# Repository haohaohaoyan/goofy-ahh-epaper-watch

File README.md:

# Neutron e-paper watch - (relatively) low-cost interactive e-paper wristwatch for the nerdy

A developer/tech nerd friendly wristwatch powered by an ESP32 S3 MINI 1, uses an e-paper display for power efficiency, and a 2000mAh battery for all-day use. It's supposed to provide both the features that a regular watch is supposed to have, while also having smartwatch functions and IO pins to leverage the power of the ESP32 microcontroller. I really wanted to make myself a wristwatch that I could use and carry around in everyday life. I was initially inspired by that really expensive and prebuilt CircuitMess watch, but it lacked the DIY process and developer tools that I wanted (so no PineTime from Flavortown either). I also was bored and wanted to make another hardware project after Hackpad, and I started noticing how much I needed a watch because I got used to borrowing my mom's and forgetting the time afterward. Plus, it just looks cool. The e-paper screen was added for the power advantage over OLED, not drawing power asides from time changes. It made the driver bit more complex (because I didn't want to occupy more space with a drop-in driver module), but might have some orientation issues. The battery was initially going to be 500mAh, but that was much too little and I chose a much larger battery to carry a charge that should last all day at the cost of more space. I think that this will be a rewarding project and a well-functioning timepiece, but that will be settled after I order. 

Current features: 
- 1.54 inch e-paper display
- 1200 mAh Li-po battery which should have about a full day's worth of life, orange LED charging indicator
- Automatic device sleeping when not used (this takes advantage of the e-paper display to keep displaying time)
- USB-C charging and data transfer
- ESP32 S3 MINI 1 powered, for internet and Bluetooth
- Automatically syncs time with NTP every 6 hours (planned in firmware)
- 8-pin female IO pin row, with 1 ground, 1 3.3v, and 6 IO pins.
- 2 IO buttons, labeled A and B in the style of the Game Boy
- Reset and boot buttons for programming
- Hopefully won't explode (IMPORTANT)
- Hopefully won't revolt and kill me (ALSO IMPORTANT)

Firmware is currently untested (asides from the timekeeping loop) and is only there for submission purposes. It is currently in CircuitPython but I will probably rewrite it in C at one point.

Assembly notes (so far): Snip off legs on JST-PH receptacle after soldering, apply Kapton tape to the side of the battery that will lie in contact with the board, apply Kapton tape to backside of e-paper screen, use DOUBLE SIDED FOAM TAPE??? PCB should snap into case

## Schematic

## PCB
Note: the PCB is 66x36mm

3D render:

## Case

## BOM in BOM.csv, but here anyway (used a md generator, sorry)

|FIELD1                                                         |FIELD2        |FIELD3          |FIELD4                                                                                              |FIELD5     |FIELD6       |FIELD7                  |FIELD8                                                                                                                                                                                             |
|---------------------------------------------------------------|--------------|----------------|----------------------------------------------------------------------------------------------------|-----------|-------------|------------------------|---------------------------------------------------------------------------------------------------------------------------------------------------------------------------------------------------|
|Item / component                                               |Quantity      |Parts on PCB    |Link                                                                                                |Source     |Cost per unit|Total cost (no shipping)|Notes                                                                                                                                                                                              |
|PCB                                                            |5 (JLCPCB MOQ)|N/A             |JLCPCB                                                                                              |JLCPCB     |$3.74        |$18.70                  |Global Standard Direct Line, ENIG plated for reflowing. Shipping is $10.67                                                                                                                         |
|PCB Stencil                                                    |1             |N/A             |JLCPCB                                                                                              |JLCPCB     |$3.07        |$3.07                   |80x40mm to reduce weight, shipped with PCB                                                                                                                                                         |
|Case                                                           |1             |N/A             |See repository                                                                                      |           |             |                        |STEP & FreeCAD files on repository                                                                                                                                                                 |
|1200 mAh 603450 Lithium-ion polymer battery                    |1             |N/A             |https://www.amazon.com/1200mAh-Battery-Rechargeable-Lithium-Connector/dp/B09FLG39NX                 |Amazon     |$8.99        |$8.99                   |Battery JST-PH 2-pin connector may have reversed polarity, ground should be on left when slot side is facing up. Be careful or risk blowing up your room!                                          |
|1.54 inch 200x200 pixel bare e-paper display                   |1             |N/A             |https://www.waveshare.com/product/1.54inch-e-paper.htm                                              |Waveshare  |$5.99        |$5.99                   |Ribbon cable pins should be facing upwards. Don't order one of the breakout board ones!                                                                                                            |
|16mm one-piece watch strap                                     |1             |N/A             |https://www.amazon.com/WOCCI-Military-One-piece-Ballistic-Buckle/dp/B0CTSCVBB4?th=1                 |Amazon     |$6.99        |$6.99                   |Optional. Really, any strip of fabric that fits should be OK.                                                                                                                                      |
|ESP32-S3-MINI-1-N8 microcontroller                             |1             |U1              |https://www.lcsc.com/product-detail/C2913206.html                                                   |LCSC       |$4.73        |$4.73                   |                                                                                                                                                                                                   |
|G-Switch GT-USB-7010ASV USB-C receptacle                       |5 (LCSC MOQ)  |J4 or USB-C     |https://www.lcsc.com/product-detail/C2988369.html                                                   |LCSC       |$0.13        |$0.65                   |LCSC MOQ is 5, you can find another one but fitting the same footprint isn't guaranteed. I don't think it's too big of a deal considering how cheap it is and how I'll probably have to reuse them.|
|JUSHUO AFC07-S24FCA-00 24-pin .5mm pitch ribbon cable connector|5 (LCSC MOQ)  |J5              |https://www.lcsc.com/product-detail/C262567.html                                                    |LCSC       |$0.13        |$0.65                   |LCSC MOQ is 5. Make sure the contacts are on the bottom!                                                                                                                                           |
|MCP73831T-2ACI/OT battery charigng IC                          |1             |U2              |https://www.digikey.com/en/products/detail/microchip-technology/MCP73831T-2ACI-OT/964301            |Digikey    |$0.76        |$0.76                   |                                                                                                                                                                                                   |
|RT9080-33GJ5 3.3V LDO IC                                       |1             |U3              |https://www.digikey.com/en/products/detail/richtek-usa-inc/RT9080-33GJ5/6161634                     |Digikey    |$0.28        |$0.28                   |                                                                                                                                                                                                   |
|RV-3028-C7 real-time clock IC                                  |1             |U4              |https://www.digikey.com/en/products/detail/micro-crystal-ag/RV-3028-C7-32-768KHZ-1PPM-TA-QA/10499248|Digikey    |$2.52        |$2.52                   |                                                                                                                                                                                                   |
|JST-PH 2 pin right angle receptacle                            |1             |J3              |https://www.digikey.com/en/products/detail/jst-sales-america-inc/S2B-PH-K-S/926626                  |Digikey    |$0.11        |$0.11                   |Snip legs half off during assembly to kinda not stab the battery                                                                                                                                   |
|USBLC6-2CS6 USB ESD diode array                                |5 (LCSC MOQ)  |U5              |https://www.lcsc.com/product-detail/C7519.html                                                      |LCSC       |$0.18        |$0.91                   |Digikey has the same with MOQ 1 at $0.54 per, but this is like barely more expensive and has 4 extra. I'm probably going to use these with the extra USB-C plugs anyway.                           |
|Si1308EDL N-channel MOSFET                                     |1             |Q1              |https://www.digikey.com/en/products/detail/vishay-siliconix/SI1308EDL-T1-GE3/4876435                |Digikey    |$0.62        |$0.62                   |Change from GE3 to BE3 if out of stock. They are functionallly and economically identical but GE3 is greener.                                                                                      |
|0603 SMD orange LED                                            |1             |D2              |https://www.digikey.com/en/products/detail/ams-osram-usa-inc/LO-Q976-PS-25-0-20-R18/1227953         |Digikey    |$0.14        |$0.14                   |I like orange. Change it if you want.                                                                                                                                                              |
|MBR0530T3G Schottky diode                                      |5             |D1, D3-6        |https://www.digikey.com/en/products/detail/onsemi/MBR0530T3G/1477144                                |Digikey    |$0.29        |$1.45                   |                                                                                                                                                                                                   |
|GG0603052R542P ESD TVS bidirectional Zener diode               |1             |D7              |https://www.digikey.com/en/products/detail/kyocera-avx/GG0603052R542P/14552136                      |Digikey    |$0.23        |$0.23                   |This was the only suitable one that was larger than an ant's torso. I want to hand solder???                                                                                                       |
|10uH 10mA SMD 276mOhm inductor                                 |1             |L1              |https://www.digikey.com/en/products/detail/bourns-inc/SRN3015-100M/2756105                          |Digikey    |$0.38        |$0.38                   |Larger displays require 68uH & 47uH, but mine's tiny so 10uH should be fine (it's used by GoodDisplay & Adafruit on their size-specific driver boards)                                             |
|0.1 uF 0805 SMD capacitor                                      |3             |C16, C18, C19   |https://www.digikey.com/en/products/detail/samsung-electro-mechanics/CL21B104KBCNNNC/3886661        |Digikey    |$0.10        |$0.20                   |                                                                                                                                                                                                   |
|1 uF 0805 SMD capacitor                                        |11            |C3-10, C13-15   |https://www.digikey.com/en/products/detail/samsung-electro-mechanics/CL21B105KAFNNNE/3886724        |Digikey    |$0.10        |$0.54                   |                                                                                                                                                                                                   |
|4.7 uF 0805 SMD capacitor                                      |4             |C1, C2, C11, C12|https://www.digikey.com/en/products/detail/samsung-electro-mechanics/CL21A475KAQNNNE/3886902        |Digikey    |$0.11        |$0.44                   |                                                                                                                                                                                                   |
|22 uF 0805 SMD capacitor                                       |1             |C17             |https://www.digikey.com/en/products/detail/samsung-electro-mechanics/CL21A226KQCLRNC/5961171        |Digikey    |$0.14        |$0.14                   |                                                                                                                                                                                                   |
|3 ohm 0603 SMD resistor                                        |1             |R6              |https://www.digikey.com/en/products/detail/panasonic-industry/ERJ-3GEYJ3R0V/282122                  |Digikey    |$0.10        |$0.10                   |                                                                                                                                                                                                   |
|500 ohm 0603 SMD resistor                                      |1             |R4              |https://www.digikey.com/en/products/detail/yageo/RT0603BRD07500RL/17019950                          |Digikey    |$0.10        |$0.10                   |                                                                                                                                                                                                   |
|2k ohm 0603 SMD resistor                                       |1             |R3              |https://www.digikey.com/en/products/detail/panasonic-industry/ERJ-3EKF2001V/196183                  |Digikey    |$0.10        |$0.10                   |                                                                                                                                                                                                   |
|4.7k ohm 0603 SMD resistor                                     |2             |R1, R2          |https://www.digikey.com/en/products/detail/stackpole-electronics-inc/RMCF0603FT4K70/1760998         |Digikey    |$0.10        |$0.20                   |                                                                                                                                                                                                   |
|5.1k ohm 0603 SMD resistor                                     |2             |R7, R8          |https://www.digikey.com/en/products/detail/yageo/RC0603FR-075K1L/727268                             |Digikey    |$0.10        |$0.20                   |                                                                                                                                                                                                   |
|10k ohm 0603 SMD resistor                                      |6             |R5, R9-R13      |https://www.digikey.com/en/products/detail/yageo/RC0603FR-0710KL/726880                             |Digikey    |$0.10        |$0.60                   |                                                                                                                                                                                                   |
|1x8 2.54mm pitch header pins, male or female                   |1             |J2/IO pins      |https://www.digikey.com/en/products/detail/würth-elektronik/61300811821/17737805                    |Digikey    |$0.40        |$0.40                   |Optional and can be left blank, really. Low profile ones are best but the regular 8.51mm insulator height ones are cheapest.                                                                       |
|Shipping (estimate)                                            |N/A           |N/A             |All sources                                                                                         |All sources|$25          |$25                     |Pretty optimistic estimate                                                                                                                                                                         |
|                                                               |              |                |                                                                                                    |           |*Total*        |*$85.19*                  |                                                                                                                                                                                                   |

It comes to $57.66 minimum without shipping, including PCB, stencil, and watch strap. Not great but better than the CircuitMess's $130 and the PebbleTime 2's $225. 

It's probably a good idea to order 1-2 extra of the small components, like the capacitors, resistors, and diodes. The crystal could also have a spare because of how easy it is to fry them.

Also probably needed: PCB conformal coating for waterproofing and Kapton tape

## Extra Credits:

yassin for looking over my battery circuit and pointing out that I tried to shove 5v into 3v3 (I know I'm an idiot) and looking at my crystal

Kai Pereira for responding to my questions on the hardware slack and for his Overglade badge which I used as a bit of a reference to make sure I'm not doing anything stupid with the e-paper

Waveshare for their e-paper driver (pretty much dropped in the entire schematic for that but removed the compability switches, do NOT give me any credit for that) (I cannot stress enough that all credit should go to them because I literally do not know anything about e-paper displays. Like, I understand a bit about what the parts are doing but not too much, really. That's my fault.)

Matters of Intrigue for a good video on the ESP32 S3's timing (https://www.youtube.com/watch?v=fZAR8WTKiSg)

OCGC (a bunch of my friends shoved onto a Google Chat) for name help

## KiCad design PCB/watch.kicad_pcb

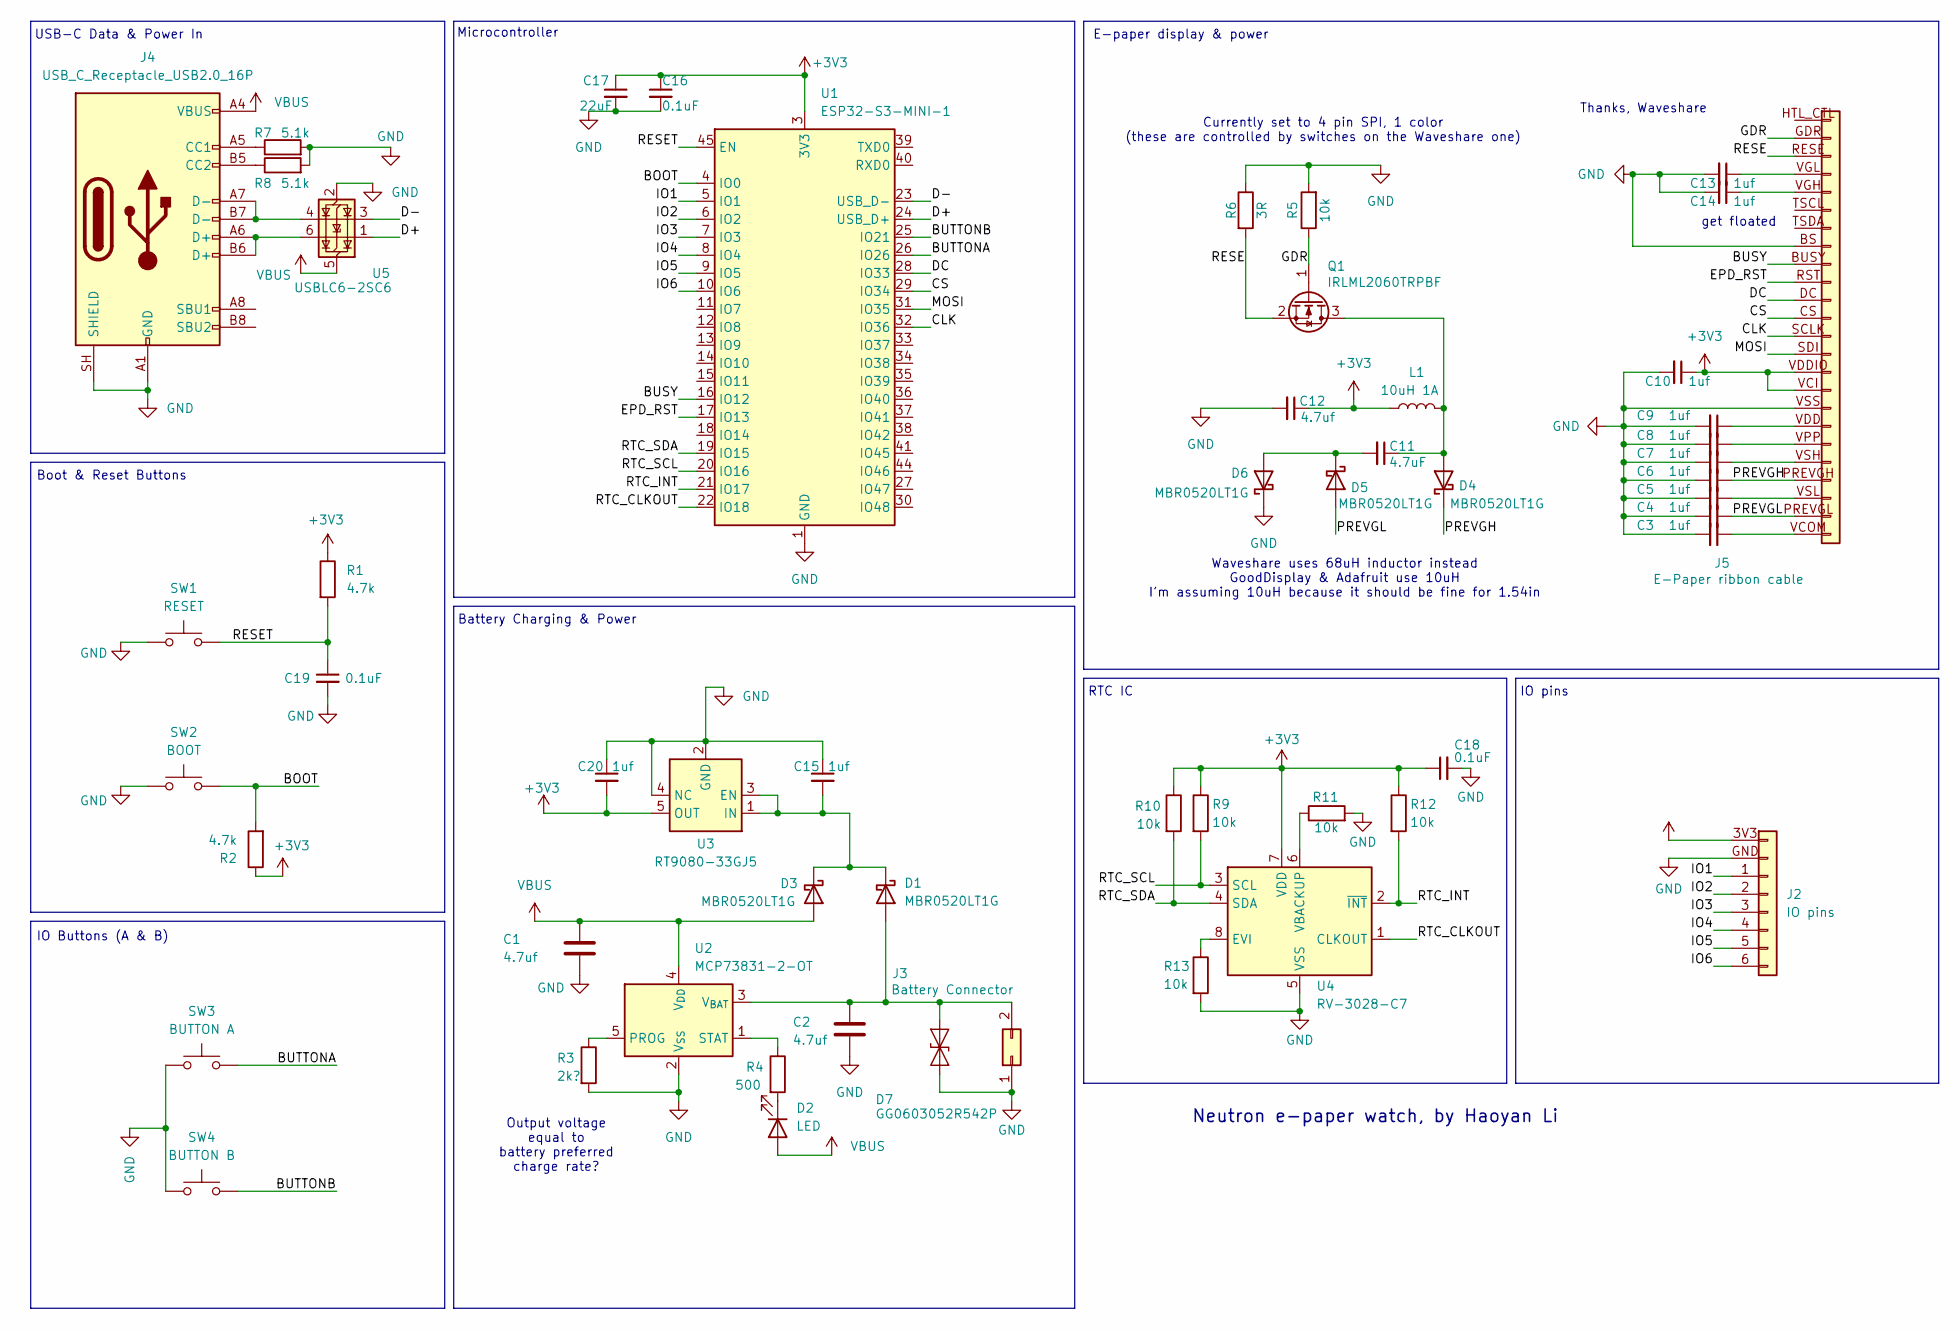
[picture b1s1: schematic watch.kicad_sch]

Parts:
C1, C2, C12: 4.7uf; C_0805_2012Metric_Pad1.18x1.45mm_HandSolder
C3, C4, C5, C6, C7, C8, C9, C10, C13, C14, C15, C20: 1uf; C_0603_1608Metric_Pad1.08x0.95mm_HandSolder
C11: 4.7uF; C_0805_2012Metric_Pad1.18x1.45mm_HandSolder
C16, C18, C19: 0.1uF; C_0805_2012Metric_Pad1.18x1.45mm_HandSolder
C17: 22uF; C_0805_2012Metric_Pad1.18x1.45mm_HandSolder
D1, D3, D4, D5, D6: MBR0520LT1G; D_SOD-123
D2: LED; LED_0603_1608Metric_Pad1.05x0.95mm_HandSolder
D7: GG0603052R542P; D_0603_1608Metric_Pad1.05x0.95mm_HandSolder
J2: IO pins; PinHeader_1x08_P2.54mm_Vertical
J3: Battery Connector; JST_PH_S2B-PH-K_1x02_P2.00mm_Horizontal
J4: USB_C_Receptacle_USB2.0_16P; USB_C_Receptacle_G-Switch_GT-USB-7010ASV
J5: E-Paper ribbon cable; Jushuo_AFC07-S24FCA-00_1x24-1MP_P0.50_Horizontal
L1: 10uH 1A; IND_BOURNS_SRN3015
Q1: IRLML2060TRPBF; SOT-323_SC-70
R1, R2: 4.7k; R_0603_1608Metric_Pad0.98x0.95mm_HandSolder
R3: 2k?; R_0603_1608Metric_Pad0.98x0.95mm_HandSolder
R4: 500; R_0603_1608Metric_Pad0.98x0.95mm_HandSolder
R5, R9, R10, R11, R12, R13: 10k; R_0603_1608Metric_Pad0.98x0.95mm_HandSolder
R6: 3R; R_0603_1608Metric_Pad0.98x0.95mm_HandSolder
R7, R8: 5.1k; R_0603_1608Metric_Pad0.98x0.95mm_HandSolder
SW1: RESET; SW-SMD_L3.9-W3.0-P4.45 C455280
SW2: BOOT; SW-SMD_L3.9-W3.0-P4.45 C455280
SW3: BUTTON A; SW-SMD_L3.9-W3.0-P4.45 C455280
SW4: BUTTON B; SW-SMD_L3.9-W3.0-P4.45 C455280
U1: ESP32-S3-MINI-1; ESP32-S2-MINI-1
U2: MCP73831-2-OT; SOT-23-5
U3: RT9080-33GJ5; SOT-23-5
U4: RV-3028-C7; MicroCrystal_C7_SON-8_1.5x3.2mm_P0.9mm
U5: USBLC6-2SC6; SOT-23-6

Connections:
+3V3: C10.1, C12.1, C16.1, C17.1, C18.1, C20.2, J2.3V3 (Pin_1), J5.VCI (Pin_16), J5.VDDIO (Pin_15), L1.1, R1.1, R2.1, R9.1, R10.1, R12.1, U1.3 (3V3), U3.5 (OUT), U4.7 (VDD); also elsewhere on the board
/BOOT: R2.2, SW2.2, U1.4 (IO0); also elsewhere on the board
/BUSY: J5.BUSY (Pin_9), U1.16 (IO12); also elsewhere on the board
/BUTTONA: SW3.2, U1.26 (IO26); also elsewhere on the board
/BUTTONB: SW4.2, U1.25 (IO21); also elsewhere on the board
/CLK: J5.SCLK (Pin_13), U1.32 (IO36); also elsewhere on the board
/CS: J5.CS (Pin_12), U1.29 (IO34); also elsewhere on the board
/D+: U1.24 (USB_D+), U5.1 (I/O1); also elsewhere on the board
/D-: U1.23 (USB_D-), U5.3 (I/O2); also elsewhere on the board
/DC: J5.DC (Pin_11), U1.28 (IO33); also elsewhere on the board
/EPD_RST: J5.RST (Pin_10), U1.17 (IO13); also elsewhere on the board
/GDR: J5.GDR (Pin_2), Q1.1 (G), R5.1
/MOSI: J5.SDI (Pin_14), U1.31 (IO35); also elsewhere on the board
/PREVGH: C6.1, D4.1 (K), J5.PREVGH (Pin_21)
/PREVGL: C4.1, D5.2 (A), J5.PREVGL (Pin_23)
/RESE: J5.RESE (Pin_3), Q1.2 (S), R6.2
/RESET: C19.1, R1.2, SW1.2, U1.45 (EN); also elsewhere on the board
/RTC_CLKOUT: U1.22 (IO18), U4.1 (CLKOUT); also elsewhere on the board
/RTC_INT: R12.2, U1.21 (IO17), U4.2 (~INT); also elsewhere on the board
/RTC_SCL: R9.2, U1.20 (IO16), U4.3 (SCL); also elsewhere on the board
/RTC_SDA: R10.2, U1.19 (IO15), U4.4 (SDA); also elsewhere on the board
GND: C1.2, C2.2, C3.2, C4.2, C5.2, C6.2, C7.2, C8.2, C9.2, C10.2, C12.2, C13.2, C14.2, C15.1, C16.2, C17.2, C18.2, C19.2, C20.1, D6.1 (K), D7.1 (A1), J2.GND (Pin_2), J3.1, J4.A1 (GND), J4.A12 (GND), J4.B1 (GND), J4.B12 (GND), J4.SH (SHIELD), J5.BS (Pin_8), J5.VSS (Pin_17), R3.2, R5.2, R6.1, R7.2, R8.2, R11.2, R13.2, SW1.1, SW2.1, SW3.1, SW4.1, U1.1 (GND), U1.2 (GND), U1.42 (GND), U1.43 (GND), U1.46 (GND), U1.47 (GND), U1.48 (GND), U1.49 (GND), U1.50 (GND), U1.51 (GND), U1.52 (GND), U1.53 (GND), U1.54 (GND), U1.55 (GND), U1.56 (GND), U1.57 (GND), U1.58 (GND), U1.59 (GND), U1.60 (GND), U1.61 (GND), U1.62 (GND), U1.63 (GND), U1.64 (GND), U1.65 (GND), U2.2 (V_{SS}), U3.2 (GND), U3.4 (NC), U4.5 (VSS), U5.2 (GND); also elsewhere on the board
unnamed: C2.1, D1.2 (A), D7.2 (A2), J3.2, U2.3 (V_{BAT})
unnamed: C15.2, D1.1 (K), D3.1 (K), U3.1 (IN), U3.3 (EN)
unnamed: D2.1 (K), R4.2
unnamed: C11.1, D4.2 (A), L1.2, Q1.3 (D)
unnamed: C11.2, D5.1 (K), D6.2 (A)
unnamed: J2.1 (Pin_3), U1.5 (IO1)
unnamed: J2.2 (Pin_4), U1.6 (IO2)
unnamed: J2.3 (Pin_5), U1.7 (IO3)
unnamed: J2.4 (Pin_6), U1.8 (IO4)
unnamed: J2.5 (Pin_7), U1.9 (IO5)
unnamed: J2.6 (Pin_8), U1.10 (IO6)
unnamed: J4.A5 (CC1), R7.1
unnamed: J4.B5 (CC2), R8.1
unnamed: J4.A6 (D+), J4.B6 (D+), U5.6 (I/O1)
unnamed: J4.A7 (D-), J4.B7 (D-), U5.4 (I/O2)
unnamed: C13.1, J5.VGL (Pin_4)
unnamed: C14.1, J5.VGH (Pin_5)
unnamed: C9.1, J5.VDD (Pin_18)
unnamed: C8.1, J5.VPP (Pin_19)
unnamed: C7.1, J5.VSH (Pin_20)
unnamed: C5.1, J5.VSL (Pin_22)
unnamed: C3.1, J5.VCOM (Pin_24)
unnamed: R3.1, U2.5 (PROG)
unnamed: R4.1, U2.1 (STAT)
unnamed: R13.1, U4.8 (EVI)
unnamed: R11.1, U4.6 (VBACKUP)
VBUS: C1.1, D2.2 (A), D3.2 (A), J4.A4 (VBUS), J4.A9 (VBUS), J4.B4 (VBUS), J4.B9 (VBUS), U2.4 (V_{DD}), U5.5 (VBUS)

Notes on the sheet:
IO pins
E-paper display & power
Boot & Reset Buttons
USB-C Data & Power In
RTC IC
get floated
Thanks, Waveshare
IO Buttons (A & B)
Battery Charging & Power
Currently set to 4 pin SPI, 1 color (these are controlled by switches on the Waveshare one)
Waveshare uses 68uH inductor instead GoodDisplay & Adafruit use 10uH I'm assuming 10uH because it should be fine for 1.54in
Microcontroller
Output voltage equal to battery preferred charge rate?
Neutron e-paper watch, by Haoyan Li

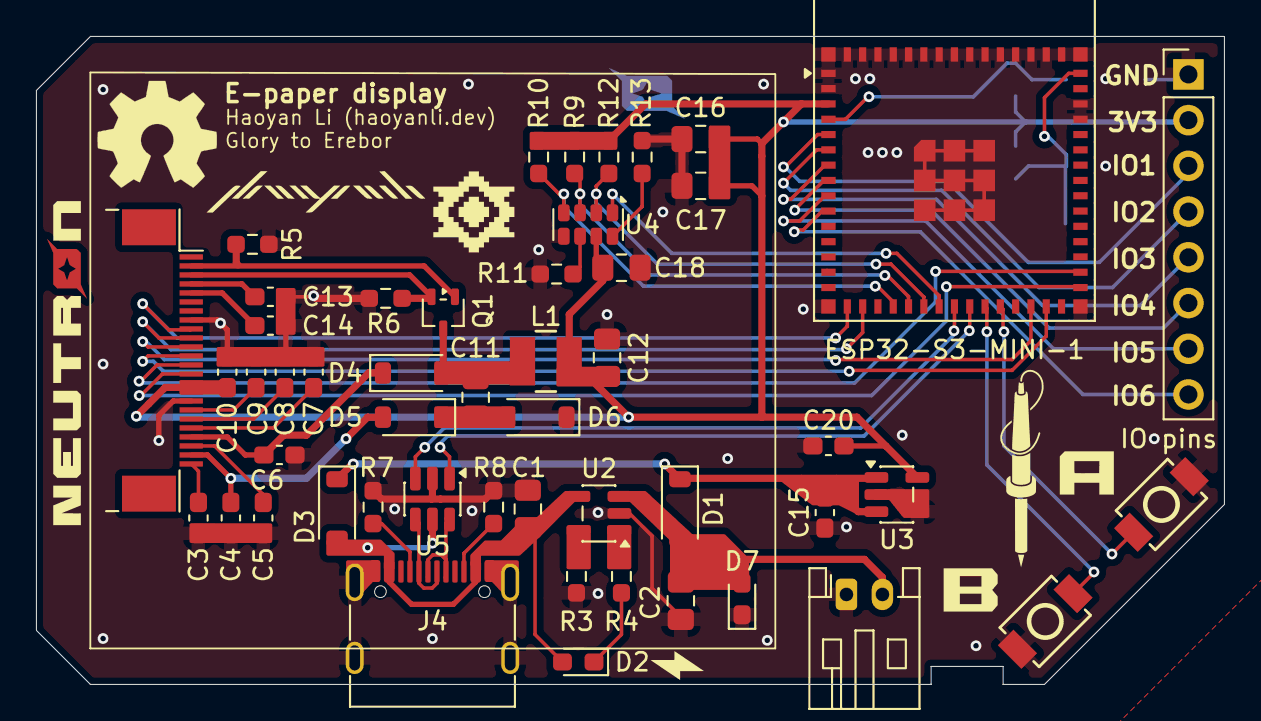
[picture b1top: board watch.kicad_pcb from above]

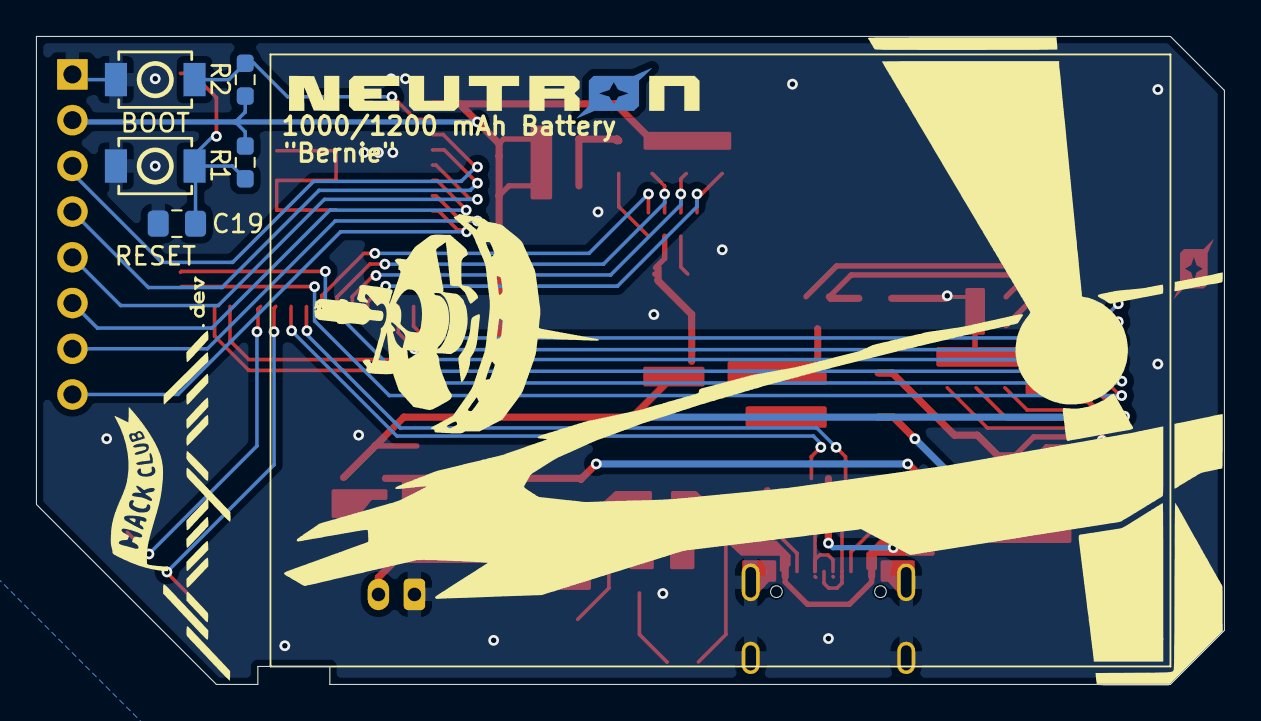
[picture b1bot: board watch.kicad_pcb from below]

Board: 2 copper layers, 66.0 x 36.0 mm, 55 parts (5 on the bottom side), 49 nets.

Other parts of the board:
BOOT: BOOT; SW-SMD_L3.9-W3.0-P4.45 C455280
ESP32-S3-MINI-1: ESP32-S3-MINI-1; ESP32-S2-MINI-1
IO pins: IO pins; PinHeader_1x08_P2.54mm_Vertical
RESET: RESET; SW-SMD_L3.9-W3.0-P4.45 C455280

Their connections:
+3V3: ESP32-S3-MINI-1.3 (3V3), IO pins.3V3 (Pin_1); also elsewhere on the board
/BOOT: BOOT.2, ESP32-S3-MINI-1.4 (IO0); also elsewhere on the board
/BUSY: ESP32-S3-MINI-1.16 (IO12); also elsewhere on the board
/BUTTONA: ESP32-S3-MINI-1.26 (IO26); also elsewhere on the board
/BUTTONB: ESP32-S3-MINI-1.25 (IO21); also elsewhere on the board
/CLK: ESP32-S3-MINI-1.32 (IO36); also elsewhere on the board
/CS: ESP32-S3-MINI-1.29 (IO34); also elsewhere on the board
/D+: ESP32-S3-MINI-1.24 (USB_D+); also elsewhere on the board
/D-: ESP32-S3-MINI-1.23 (USB_D-); also elsewhere on the board
/DC: ESP32-S3-MINI-1.28 (IO33); also elsewhere on the board
/EPD_RST: ESP32-S3-MINI-1.17 (IO13); also elsewhere on the board
/IO1: ESP32-S3-MINI-1.5 (IO1), IO pins.1 (Pin_3)
/IO2: ESP32-S3-MINI-1.6 (IO2), IO pins.2 (Pin_4)
/IO3: ESP32-S3-MINI-1.7 (IO3), IO pins.3 (Pin_5)
/IO4: ESP32-S3-MINI-1.8 (IO4), IO pins.4 (Pin_6)
/IO5: ESP32-S3-MINI-1.9 (IO5), IO pins.5 (Pin_7)
/IO6: ESP32-S3-MINI-1.10 (IO6), IO pins.6 (Pin_8)
/MOSI: ESP32-S3-MINI-1.31 (IO35); also elsewhere on the board
/RESET: ESP32-S3-MINI-1.45 (EN), RESET.2; also elsewhere on the board
/RTC_CLKOUT: ESP32-S3-MINI-1.22 (IO18); also elsewhere on the board
/RTC_INT: ESP32-S3-MINI-1.21 (IO17); also elsewhere on the board
/RTC_SCL: ESP32-S3-MINI-1.20 (IO16); also elsewhere on the board
/RTC_SDA: ESP32-S3-MINI-1.19 (IO15); also elsewhere on the board
GND: BOOT.1, ESP32-S3-MINI-1.1 (GND), ESP32-S3-MINI-1.2 (GND), ESP32-S3-MINI-1.42 (GND), ESP32-S3-MINI-1.43 (GND), ESP32-S3-MINI-1.46 (GND), ESP32-S3-MINI-1.47 (GND), ESP32-S3-MINI-1.48 (GND), ESP32-S3-MINI-1.49 (GND), ESP32-S3-MINI-1.50 (GND), ESP32-S3-MINI-1.51 (GND), ESP32-S3-MINI-1.52 (GND), ESP32-S3-MINI-1.53 (GND), ESP32-S3-MINI-1.54 (GND), ESP32-S3-MINI-1.55 (GND), ESP32-S3-MINI-1.56 (GND), ESP32-S3-MINI-1.57 (GND), ESP32-S3-MINI-1.58 (GND), ESP32-S3-MINI-1.59 (GND), ESP32-S3-MINI-1.60 (GND), ESP32-S3-MINI-1.61 (GND), ESP32-S3-MINI-1.62 (GND), ESP32-S3-MINI-1.63 (GND), ESP32-S3-MINI-1.64 (GND), ESP32-S3-MINI-1.65 (GND), IO pins.GND (Pin_2), RESET.1; also elsewhere on the board

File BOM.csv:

,,,,,,,
Item / component,Quantity,Parts on PCB,Link,Source,Cost per unit,Total cost (no shipping),Notes
PCB,5 (JLCPCB MOQ),N/A,JLCPCB,JLCPCB,$3.74,$18.70,"Global Standard Direct Line, ENIG plated for reflowing. Shipping is $10.67"
PCB Stencil,1,N/A,JLCPCB,JLCPCB,$3.07,$3.07,"80x40mm to reduce weight, shipped with PCB"
Case,1,N/A,See repository,,,,STEP & FreeCAD files on repository
1200 mAh 603450 Lithium-ion polymer battery,1,N/A,https://www.amazon.com/1200mAh-Battery-Rechargeable-Lithium-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,Amazon,$8.99,$8.99,"Battery JST-PH 2-pin connector may have reversed polarity, ground should be on left when slot side is facing up. Be careful or risk blowing up your room!"
1.54 inch 200x200 pixel bare e-paper display,1,N/A,https://www.waveshare.com/product/1.54inch-e-paper.htm,Waveshare,$5.99,$5.99,Ribbon cable pins should be facing upwards. Don't order one of the breakout board ones!
16mm one-piece watch strap,1,N/A,https://www.amazon.com/WOCCI-Military-One-piece-Ballistic-Bu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,Amazon,$6.99,$6.99,"Optional. Really, any strip of fabric that fits should be OK."
ESP32-S3-MINI-1-N8 microcontroller,1,U1,https://www.lcsc.com/product-detail/C2913206.html,LCSC,$4.73,$4.73,
G-Switch GT-USB-7010ASV USB-C receptacle,5 (LCSC MOQ),J4 or USB-C,https://www.lcsc.com/product-detail/C2988369.html,LCSC,$0.13,$0.65,"LCSC MOQ is 5, you can find another one but fitting the same footprint isn't guaranteed. I don't think it's too big of a deal considering how cheap it is and how I'll probably have to reuse them."
JUSHUO AFC07-S24FCA-00 24-pin .5mm pitch ribbon cable connector,5 (LCSC MOQ),J5,https://www.lcsc.com/product-detail/C262567.html,LCSC,$0.13,$0.65,LCSC MOQ is 5. Make sure the contacts are on the bottom!
MCP73831T-2ACI/OT battery charigng IC,1,U2,https://www.digikey.com/en/products/detail/microchip-technol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,Digikey,$0.76,$0.76,
RT9080-33GJ5 3.3V LDO IC,1,U3,https://www.digikey.com/en/products/detail/richtek-usa-inc/R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,Digikey,$0.28,$0.28,
RV-3028-C7 real-time clock IC,1,U4,https://www.digikey.com/en/products/detail/micro-crystal-ag/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,Digikey,$2.52,$2.52,
JST-PH 2 pin right angle receptacle,1,J3,https://www.digikey.com/en/products/detail/jst-sales-america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,Digikey,$0.11,$0.11,Snip legs half off during assembly to kinda not stab the battery
USBLC6-2CS6 USB ESD diode array,5 (LCSC MOQ),U5,https://www.lcsc.com/product-detail/C7519.html,LCSC,$0.18,$0.91,"Digikey has the same with MOQ 1 at $0.54 per, but this is like barely more expensive and has 4 extra. I'm probably going to use these with the extra USB-C plugs anyway."
Si1308EDL N-channel MOSFET,1,Q1,https://www.digikey.com/en/products/detail/vishay-siliconix/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,Digikey,$0.62,$0.62,Change from GE3 to BE3 if out of stock. They are functionallly and economically identical but GE3 is greener.
0603 SMD orange LED,1,D2,https://www.digikey.com/en/products/detail/ams-osram-usa-inc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,Digikey,$0.14,$0.14,I like orange. Change it if you want.
MBR0530T3G Schottky diode,5,"D1, D3-6",https://www.digikey.com/en/products/detail/onsemi/MBR0530T3G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,Digikey,$0.29,$1.45,
GG0603052R542P ESD TVS bidirectional Zener diode,1,D7,https://www.digikey.com/en/products/detail/kyocera-avx/GG060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,Digikey,$0.23,$0.23,This was the only suitable one that was larger than an ant's torso. I want to hand solder???
10uH 10mA SMD 276mOhm inductor,1,L1,https://www.digikey.com/en/products/detail/bourns-inc/SRN301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,Digikey,$0.38,$0.38,"Larger displays require 68uH & 47uH, but mine's tiny so 10uH should be fine (it's used by GoodDisplay & Adafruit on their size-specific driver boards)"
0.1 uF 0805 SMD capacitor,3,"C16, C18, C19",https://www.digikey.com/en/products/detail/samsung-electro-m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,Digikey,$0.10,$0.20,
1 uF 0805 SMD capacitor,11,"C3-10, C13-15",https://www.digikey.com/en/products/detail/samsung-electro-m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,Digikey,$0.10,$0.54,
4.7 uF 0805 SMD capacitor,4,"C1, C2, C11, C12",https://www.digikey.com/en/products/detail/samsung-electro-m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,Digikey,$0.11,$0.44,
22 uF 0805 SMD capacitor,1,C17,https://www.digikey.com/en/products/detail/samsung-electro-m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,Digikey,$0.14,$0.14,
3 ohm 0603 SMD resistor,1,R6,https://www.digikey.com/en/products/detail/panasonic-industr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,Digikey,$0.10,$0.10,
500 ohm 0603 SMD resistor,1,R4,https://www.digikey.com/en/products/detail/yageo/RT0603BRD07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,Digikey,$0.10,$0.10,
2k ohm 0603 SMD resistor,1,R3,https://www.digikey.com/en/products/detail/panasonic-industr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,Digikey,$0.10,$0.10,
4.7k ohm 0603 SMD resistor,2,"R1, R2",https://www.digikey.com/en/products/detail/stackpole-electro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,Digikey,$0.10,$0.20,
5.1k ohm 0603 SMD resistor,2,"R7, R8",https://www.digikey.com/en/products/detail/yageo/RC0603FR-07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,Digikey,$0.10,$0.20,
10k ohm 0603 SMD resistor,6,"R5, R9-R13",https://www.digikey.com/en/products/detail/yageo/RC0603FR-07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,Digikey,$0.10,$0.60,
"1x8 2.54mm pitch header pins, male or female",1,J2/IO pins,https://www.digikey.com/en/products/detail/würth-elektronik/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,Digikey,$0.40,$0.40,"Optional and can be left blank, really. Low profile ones are best but the regular 8.51mm insulator height ones are cheapest."
Shipping (estimate),N/A,N/A,All sources,All sources,$25,$25,Pretty optimistic estimate
,,,,,Total,$85.19,

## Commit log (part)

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2026-05-23 starting journal
2026-05-24 update journal for today's log (image to be added)
2026-05-24 Uploaded journal image, kiCad files, and updated journal to include image
2026-05-24 Changed "1 hour and 30 minutes" to "1.5 hours" bc I don't think Forge likes that
2026-05-25 Updated journal for today, updated schematic files, started README and filled in a bit of the BOM for what is there so far
2026-05-26 E-paper display driver wired up, two IO buttons added, will do RTC next
2026-05-27 Updated BOM, started work on RTC, and added an LDO to make sure that the power output is 3V3
2026-05-28 Finished with schematic and started assigning footprints
2026-05-29 More footprints assigned
2026-05-29 Forgot an image, added
2026-05-30 Finished footprints (asides from some problems) and started on PCB.
2026-05-31 Almost done with PCB routing and placement. Also fixed some things in schematic.
2026-06-01 Finished with PCB (needs review) and added some silkscreen icons
2026-06-02 More silkscreen work, replaced the LDO for 500mA output, decided on name and started on logo.
2026-06-03 Much more work on the silkscreen art. The back is almost done and the front will be soon too.
2026-06-04 Just a few decorative changes and moving a diode.
2026-06-04 I forgot to update the KiCad files.
2026-06-05 Added a nice little spaceship to the back art
2026-06-06 FInished up art and redid BOM
2026-06-07 Generated gerbers, changed resistor footprints to 0402, and finished the components BOM
2026-06-08 More README boxes ticked and finding a watch strap
2026-06-08 I forgot the image for the latest journal entry.
2026-06-09 Checked prices on JLCPCB and PCBWay, should be close to final price now
2026-06-10 Changed capacitors to work with new LDO, updated BOM, PCB, schematic to match
2026-06-11 Changed the LDO to one that wasn't $1.7
2026-06-12 Made most of case and fixed edge cut issue
2026-06-13 Changed case to be more friendly towards the watch strap I'm planning on using and redid the e-paper driver on the PCB
2026-06-14 Started firmware, PCB should now be finalized
2026-06-15 More work with firmware, testing timekeeping
2026-06-16 Thinned the PCB by 2 millimeters and edited case to match
2026-06-17 Tested out different ways to make the timer more accurate, unfinished, see journal for next plan
2026-06-18 Finished accurate time loop
2026-06-19 Changed footprints for easier handling, swapped diodes
2026-06-20 Cleaned up more things from yesterday, changed resistance on the CC pin resistors, fixed MOSFET connections being misconnected, redid PCB AGAINNNNNNNN
2026-06-20 why does forge title autodetection hate me
2026-06-21 Made more progress on putting together a basic structure for the firmware, added a chamfer to case to accomodate for some resistors
2026-06-22 Researching new batteries to cut down on cost
2026-06-23 Updated production files and made more progress on firmware dummy
2026-06-24 Changed some trace widths, added some of the button things on the firmware, blank settings.toml for ntp which will be done tomorrow, case image added to README
2026-06-25 Starting to edit PCB to be smaller (again), changed battery capacity
2026-06-26 More cleanup, adding a 32k oscillator, moving stuff around, more traces on back woohoo
2026-06-27 Essentially done with rerouting the PCB
2026-06-28 Trying to fix any capacitance issues and moving around silkscreens
2026-06-29 Readjusted case & silkscreens, firmware DUMMY should be finished now
2026-06-30 Updated prod files, checked over README again
